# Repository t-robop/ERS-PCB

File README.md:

# ERS-PCB

## Description
Atlas，Spicaプロジェクトでのロボット用の基板．

## Requirements

### Fritzing

Fritzing Version 0.9.3 or later

### KiCad

KiCad 5.0.x or later

### Eagle

Eagle 9.x or later

### Author
multiverse2011, nishimura

### License
MIT

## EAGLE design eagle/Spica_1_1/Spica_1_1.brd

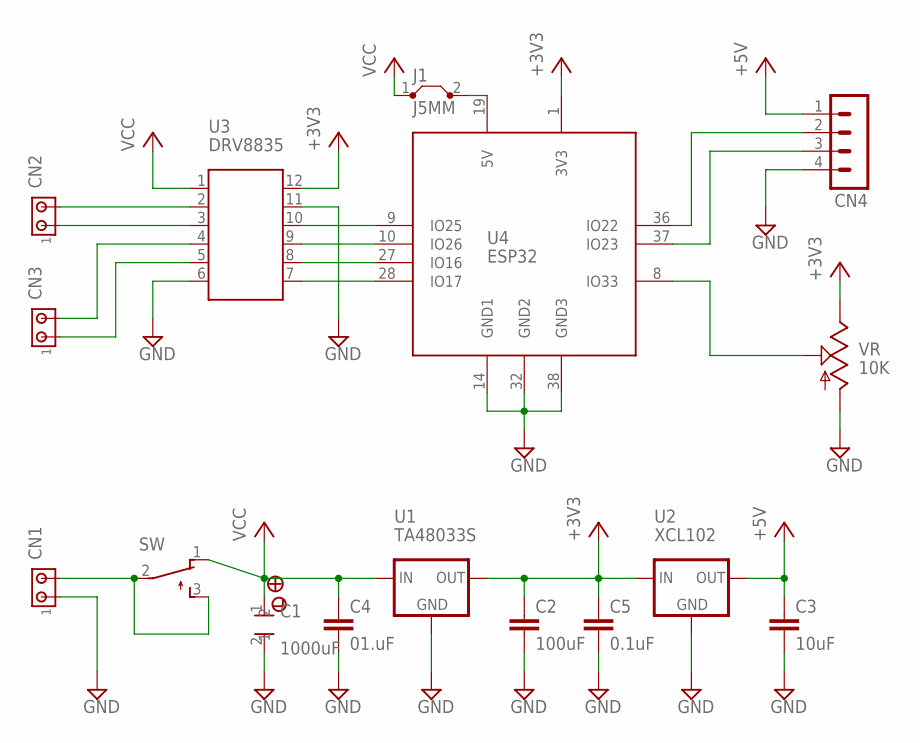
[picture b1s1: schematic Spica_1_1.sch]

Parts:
C1: 1000uF; ELECTROLYTIC_CAPACITOR_LARGE
C2: 100uF; C2.5-5
C3: 10uF; C2.5-5
C4: 01.uF; C2.5-2
C5: 0.1uF; C2.5-2
CN1, CN2, CN3: MTA02-100; 10X02MTA
CN4: MA04-1
J1: J5MM; 05
SW: TL32PO; TL3XPO
U1: TA48033S; 78XXS
U2: XCL102; 78XXS
U3: DRV8835
U4: ESP32
VR: 10K; CA6V

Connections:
+3V3: C2.1, C5.1, U1.OUT, U2.IN, U3.12, U4.1 (3V3), VR.E
+5V: C3.1, CN4.1, U2.OUT
GND: C1.2, C2.2, C3.2, C4.2, C5.2, CN1.1, CN4.4, U1.GND, U2.GND, U3.6, U3.11, U4.14 (GND1), U4.32 (GND2), U4.38 (GND3), VR.A
unnamed: CN3.2, U3.4
unnamed: CN3.1, U3.5
unnamed: U3.10, U4.9 (IO25)
unnamed: CN2.1, U3.3
unnamed: CN2.2, U3.2
unnamed: U3.9, U4.10 (IO26)
unnamed: U3.8, U4.27 (IO16)
unnamed: U3.7, U4.28 (IO17)
unnamed: CN4.2, U4.36 (IO22)
unnamed: CN4.3, U4.37 (IO23)
unnamed: U4.8 (IO33), VR.S
unnamed: J1.2, U4.19 (5V)
VCC: C1.1, C4.1, J1.1, SW.1 (O), U1.IN, U3.1
VIN: CN1.2, SW.2, SW.3 (S)

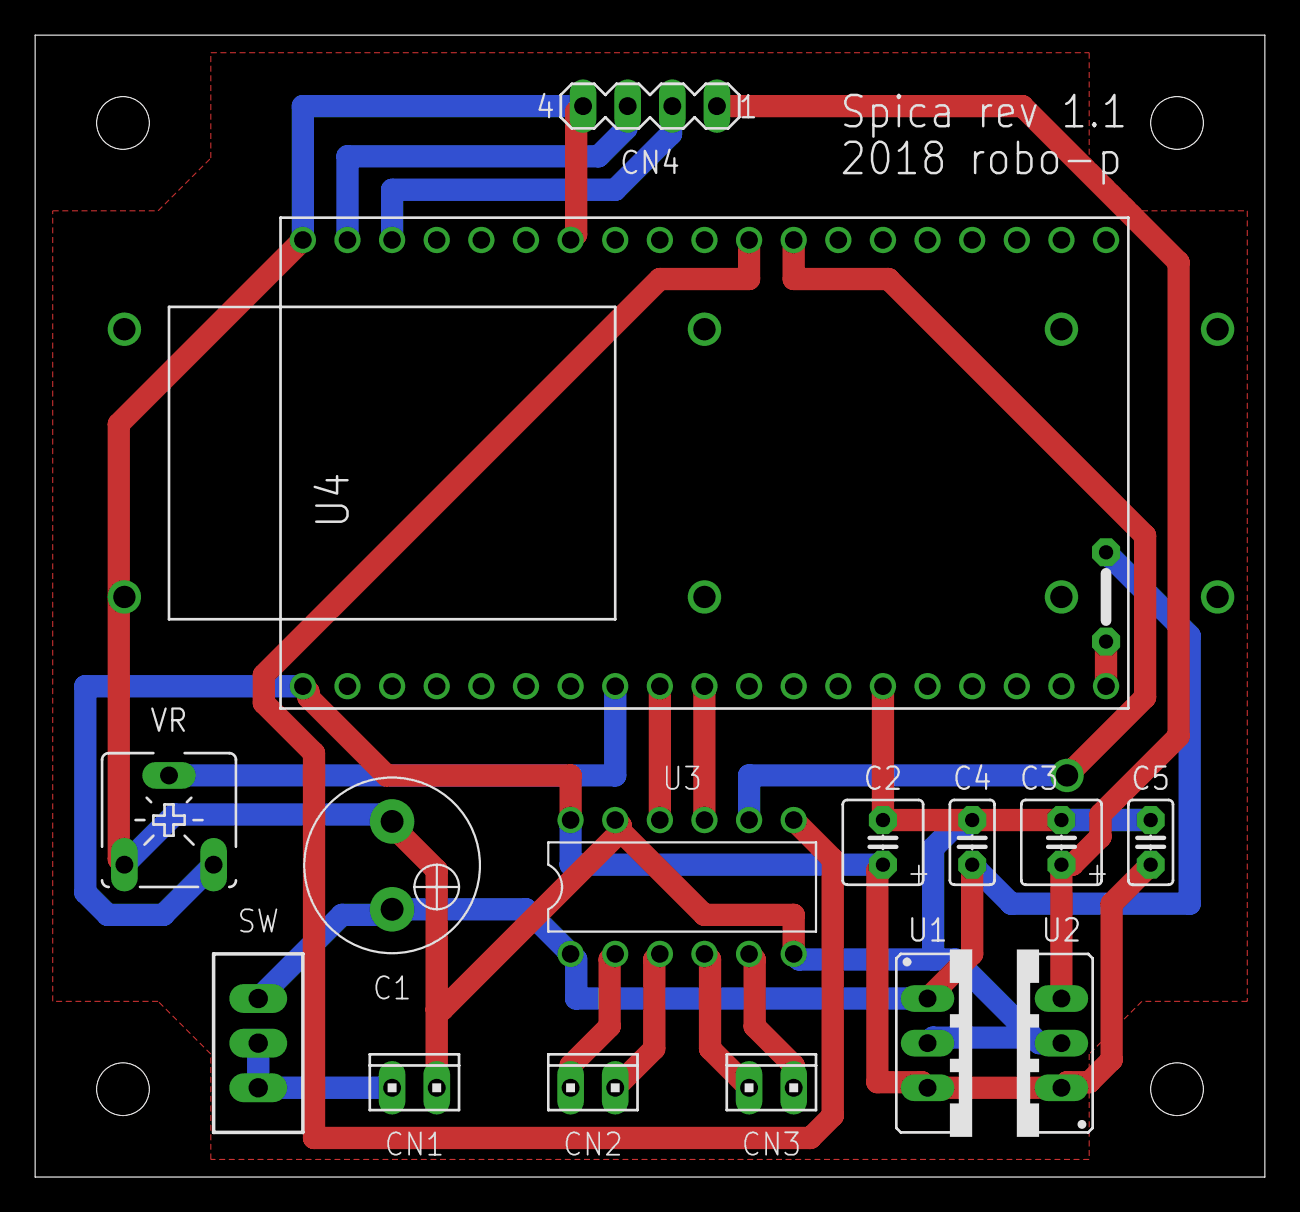
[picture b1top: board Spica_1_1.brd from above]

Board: 2 copper layers, 70.0 x 65.0 mm, 16 parts (0 on the bottom side), 17 nets.

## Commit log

2017-05-31 Create partsList
2017-05-31 Rename partsList to partsList.txt
2017-07-04 Type-Xの追加、スイッチの向きの修正
2017-10-02 Finished product edition
2017-10-18 resize&reallocation🎉
2017-10-18 Production version🎉
2017-10-31 謎のブリッジを削除
2017-10-31 旧Type-Xの削除
2018-08-15 spicaを追加
2018-08-16 半固定抵抗を追加
2018-08-16 PCB配線完了🎉
2018-08-16 Rename&整理
2018-10-04 一旦ブリッジしてるところを修正
2018-10-05 60mmx60mmに押し込んだ
2018-10-06 レイアウトの整理
2018-10-06 パーツラベルを整理
2018-10-07 Productionの1歩手前
2018-11-03 Add KiCad files
2018-11-05 Add some Akizuki parts
2018-11-05 Finish rooting
2018-11-07 Add surface GND
2018-11-07 ベタパターンを追加
2018-11-07 細かな修正
2018-11-07 Add eagle files
